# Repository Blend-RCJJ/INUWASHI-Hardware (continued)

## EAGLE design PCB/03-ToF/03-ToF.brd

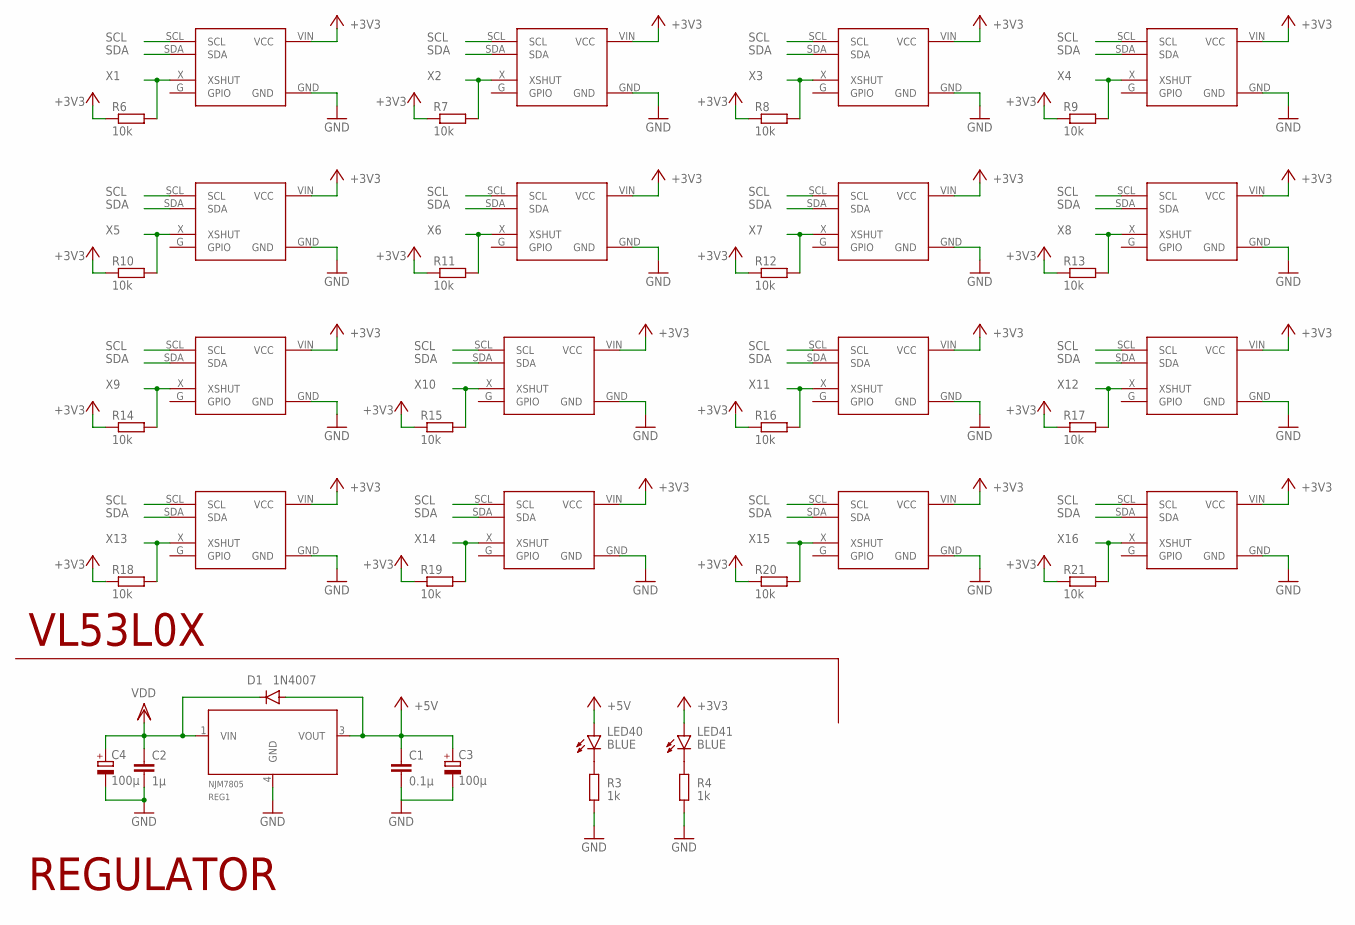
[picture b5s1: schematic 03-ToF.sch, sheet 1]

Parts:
C1: 0.1μ; C0402
C2: 1μ; C0402
C3, C4: 100μ; 153CLV-0505
D1: 1N4007; SMA-DO214AC
LED40, LED41: BLUE; SML0603
R3, R4: 1k; R0402
R6, R7, R8, R9, R10, R11, R12, R13, R14, R15, R16, R17, R18, R19, R20, R21: 10k; R0402
REG1: NJM7805; MYPARTS_D-PAK_TO252AA
VL1, VL2, VL3, VL4, VL5, VL6, VL7, VL8, VL9, VL10, VL11, VL12, VL13, VL14, VL15, VL16: VL53L0X; 1X04

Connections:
+3V3: LED41.A, R6.1, R7.1, R8.1, R9.1, R10.1, R11.1, R12.1, R13.1, R14.1, R15.1, R16.1, R17.1, R18.1, R19.1, R20.1, R21.1, VL1.VIN (VCC), VL2.VIN (VCC), VL3.VIN (VCC), VL4.VIN (VCC), VL5.VIN (VCC), VL6.VIN (VCC), VL7.VIN (VCC), VL8.VIN (VCC), VL9.VIN (VCC), VL10.VIN (VCC), VL11.VIN (VCC), VL12.VIN (VCC), VL13.VIN (VCC), VL14.VIN (VCC), VL15.VIN (VCC), VL16.VIN (VCC); also elsewhere on the board
+5V: C1.1, C3.+, D1.A, LED40.A, REG1.3 (VOUT); also elsewhere on the board
GND: C1.2, C2.2, C3.-, C4.-, R3.2, R4.2, REG1.4 (GND), VL1.GND, VL2.GND, VL3.GND, VL4.GND, VL5.GND, VL6.GND, VL7.GND, VL8.GND, VL9.GND, VL10.GND, VL11.GND, VL12.GND, VL13.GND, VL14.GND, VL15.GND, VL16.GND; also elsewhere on the board
unnamed: LED40.C, R3.1
unnamed: LED41.C, R4.1
SCL: VL1.SCL, VL2.SCL, VL3.SCL, VL4.SCL, VL5.SCL, VL6.SCL, VL7.SCL, VL8.SCL, VL9.SCL, VL10.SCL, VL11.SCL, VL12.SCL, VL13.SCL, VL14.SCL, VL15.SCL, VL16.SCL; also elsewhere on the board
SDA: VL1.SDA, VL2.SDA, VL3.SDA, VL4.SDA, VL5.SDA, VL6.SDA, VL7.SDA, VL8.SDA, VL9.SDA, VL10.SDA, VL11.SDA, VL12.SDA, VL13.SDA, VL14.SDA, VL15.SDA, VL16.SDA; also elsewhere on the board
VDD: C2.1, C4.+, D1.K (C), REG1.1 (VIN); also elsewhere on the board
X1: R6.2, VL1.X (XSHUT); also elsewhere on the board
X2: R7.2, VL2.X (XSHUT); also elsewhere on the board
X3: R8.2, VL3.X (XSHUT); also elsewhere on the board
X4: R9.2, VL4.X (XSHUT); also elsewhere on the board
X5: R10.2, VL5.X (XSHUT); also elsewhere on the board
X6: R11.2, VL6.X (XSHUT); also elsewhere on the board
X7: R12.2, VL7.X (XSHUT); also elsewhere on the board
X8: R13.2, VL8.X (XSHUT); also elsewhere on the board
X9: R14.2, VL9.X (XSHUT); also elsewhere on the board
X10: R15.2, VL10.X (XSHUT); also elsewhere on the board
X11: R16.2, VL11.X (XSHUT); also elsewhere on the board
X12: R17.2, VL12.X (XSHUT); also elsewhere on the board
X13: R18.2, VL13.X (XSHUT); also elsewhere on the board
X14: R19.2, VL14.X (XSHUT); also elsewhere on the board
X15: R20.2, VL15.X (XSHUT); also elsewhere on the board
X16: R21.2, VL16.X (XSHUT); also elsewhere on the board

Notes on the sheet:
VL53L0X
REGULATOR

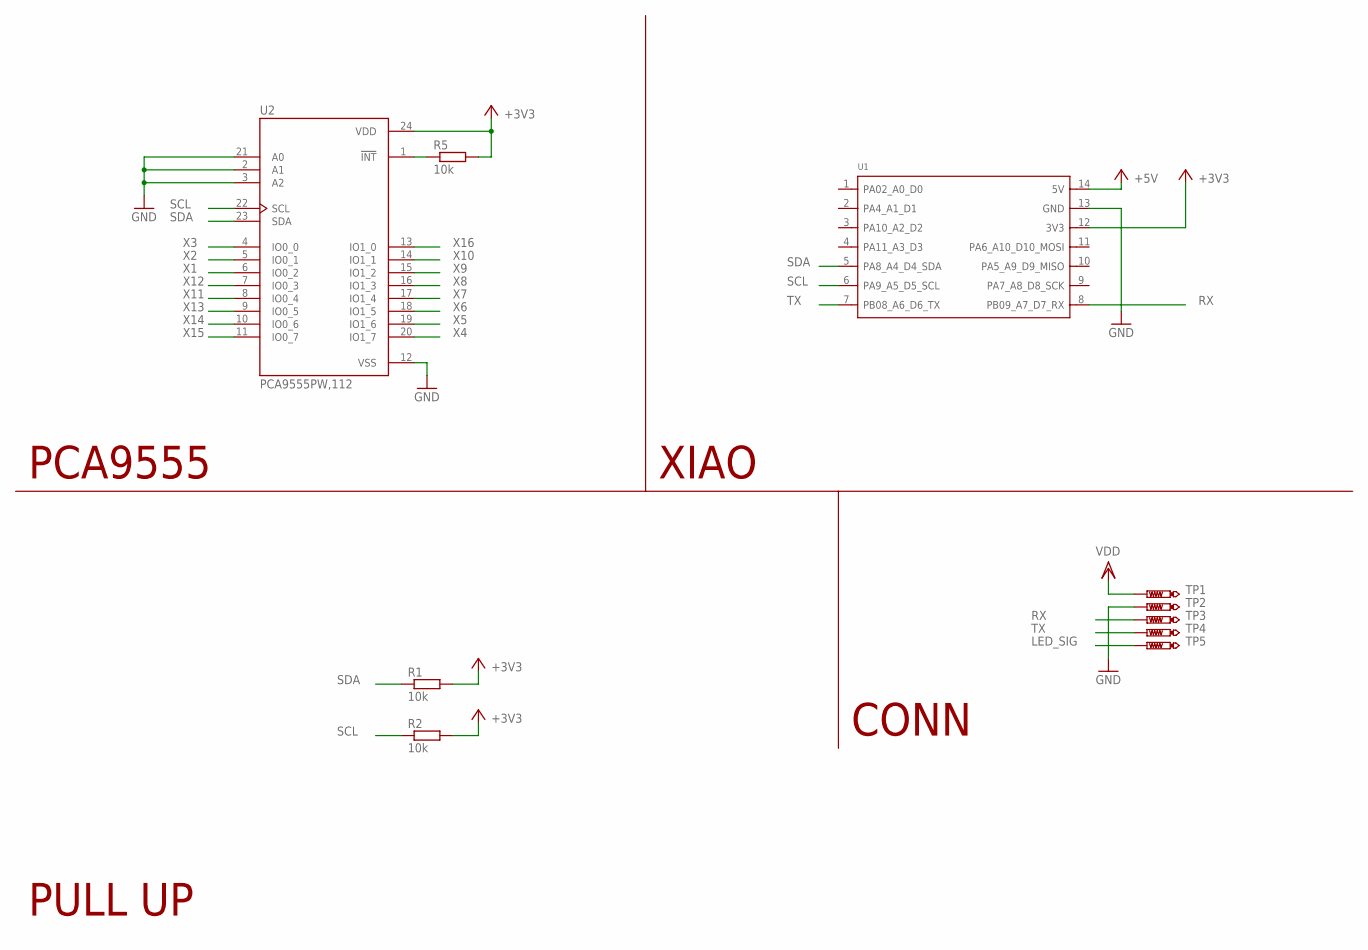
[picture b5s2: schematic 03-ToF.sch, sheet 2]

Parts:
R1, R2, R5: 10k; R0402
TP1, TP3, TP4, TP5: PTR1TP10R; TP10R
TP2: PTR1TP10SQ; TP10SQ
U1: MOUDLE-SEEEDUINO-XIAO; MOUDLE14P-2.54-21X17.8MM
U2: PCA9555PW,112; SOP65P640X110-24N

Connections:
+3V3: R1.2, R2.2, R5.2, U1.12 (3V3), U2.24 (VDD); also elsewhere on the board
+5V: U1.14 (5V); also elsewhere on the board
GND: TP2.TP, U1.13 (GND), U2.2 (A1), U2.3 (A2), U2.12 (VSS), U2.21 (A0); also elsewhere on the board
LED_SIG: TP5.TP; also elsewhere on the board
unnamed: R5.1, U2.1 (!INT)
RX: TP3.TP, U1.8 (PB09_A7_D7_RX)
SCL: R2.1, U1.6 (PA9_A5_D5_SCL), U2.22 (SCL); also elsewhere on the board
SDA: R1.1, U1.5 (PA8_A4_D4_SDA), U2.23 (SDA); also elsewhere on the board
TX: TP4.TP, U1.7 (PB08_A6_D6_TX)
VDD: TP1.TP; also elsewhere on the board
X1: U2.6 (IO0_2); also elsewhere on the board
X2: U2.5 (IO0_1); also elsewhere on the board
X3: U2.4 (IO0_0); also elsewhere on the board
X4: U2.20 (IO1_7); also elsewhere on the board
X5: U2.19 (IO1_6); also elsewhere on the board
X6: U2.18 (IO1_5); also elsewhere on the board
X7: U2.17 (IO1_4); also elsewhere on the board
X8: U2.16 (IO1_3); also elsewhere on the board
X9: U2.15 (IO1_2); also elsewhere on the board
X10: U2.14 (IO1_1); also elsewhere on the board
X11: U2.8 (IO0_4); also elsewhere on the board
X12: U2.7 (IO0_3); also elsewhere on the board
X13: U2.9 (IO0_5); also elsewhere on the board
X14: U2.10 (IO0_6); also elsewhere on the board
X15: U2.11 (IO0_7); also elsewhere on the board
X16: U2.13 (IO1_0); also elsewhere on the board

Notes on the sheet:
PCA9555
PULL UP
CONN
XIAO

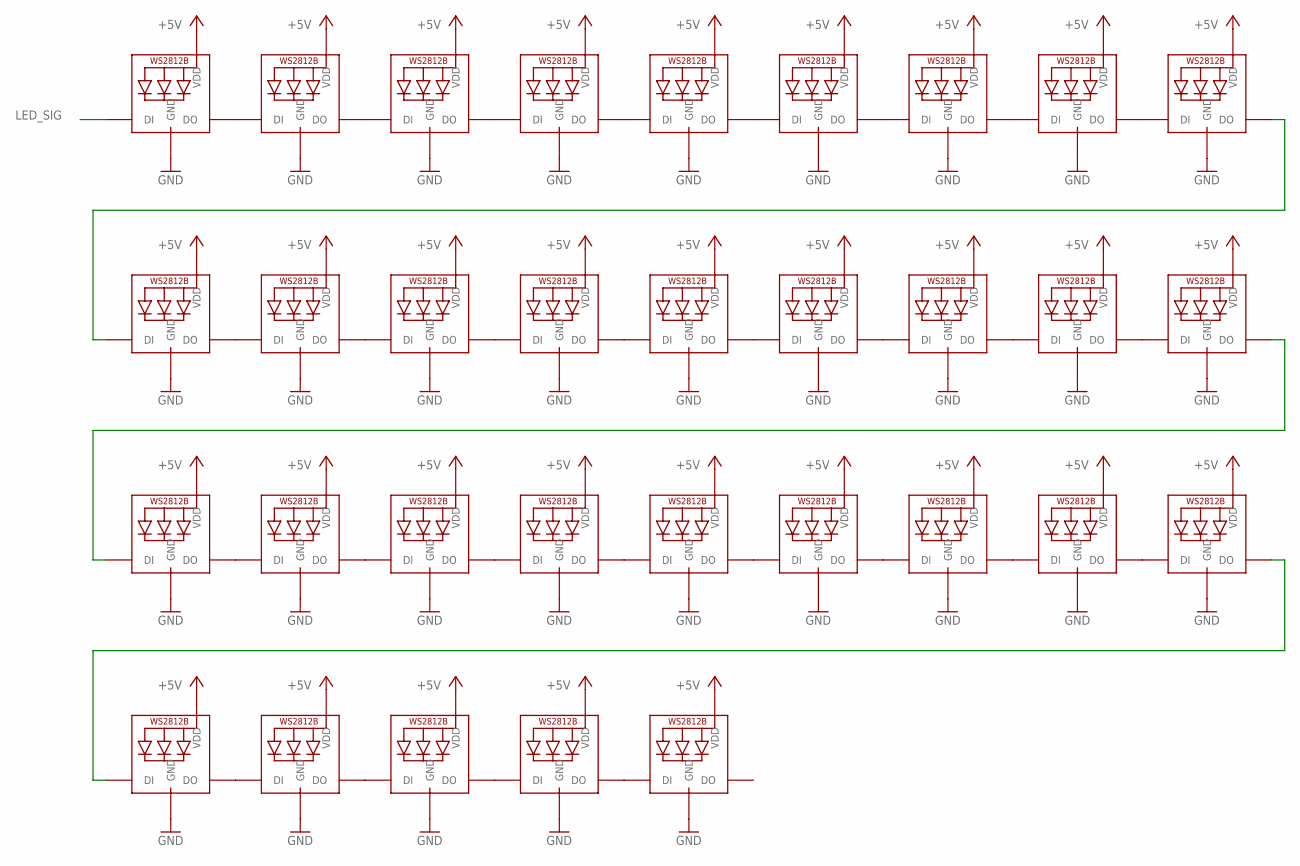
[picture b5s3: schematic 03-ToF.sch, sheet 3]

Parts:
LED1, LED2, LED3, LED4, LED5, LED6, LED7, LED8, LED9, LED10, LED11, LED12, LED13, LED14, LED15, LED16, LED17, LED18, LED19, LED20, LED21, LED22, LED23, LED24, LED25, LED26, LED27, LED28, LED29, LED30, LED31, LED32: WS2812B_5050N; WS2812B-NARROW

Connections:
+5V: LED1.1-VDD (VDD), LED2.1-VDD (VDD), LED3.1-VDD (VDD), LED4.1-VDD (VDD), LED5.1-VDD (VDD), LED6.1-VDD (VDD), LED7.1-VDD (VDD), LED8.1-VDD (VDD), LED9.1-VDD (VDD), LED10.1-VDD (VDD), LED11.1-VDD (VDD), LED12.1-VDD (VDD), LED13.1-VDD (VDD), LED14.1-VDD (VDD), LED15.1-VDD (VDD), LED16.1-VDD (VDD), LED17.1-VDD (VDD), LED18.1-VDD (VDD), LED19.1-VDD (VDD), LED20.1-VDD (VDD), LED21.1-VDD (VDD), LED22.1-VDD (VDD), LED23.1-VDD (VDD), LED24.1-VDD (VDD), LED25.1-VDD (VDD), LED26.1-VDD (VDD), LED27.1-VDD (VDD), LED28.1-VDD (VDD), LED29.1-VDD (VDD), LED30.1-VDD (VDD), LED31.1-VDD (VDD), LED32.1-VDD (VDD); also elsewhere on the board
GND: LED1.3-GND (GND), LED2.3-GND (GND), LED3.3-GND (GND), LED4.3-GND (GND), LED5.3-GND (GND), LED6.3-GND (GND), LED7.3-GND (GND), LED8.3-GND (GND), LED9.3-GND (GND), LED10.3-GND (GND), LED11.3-GND (GND), LED12.3-GND (GND), LED13.3-GND (GND), LED14.3-GND (GND), LED15.3-GND (GND), LED16.3-GND (GND), LED17.3-GND (GND), LED18.3-GND (GND), LED19.3-GND (GND), LED20.3-GND (GND), LED21.3-GND (GND), LED22.3-GND (GND), LED23.3-GND (GND), LED24.3-GND (GND), LED25.3-GND (GND), LED26.3-GND (GND), LED27.3-GND (GND), LED28.3-GND (GND), LED29.3-GND (GND), LED30.3-GND (GND), LED31.3-GND (GND), LED32.3-GND (GND); also elsewhere on the board
LED_SIG: LED1.4-DIN (DI); also elsewhere on the board
unnamed: LED1.2-DOUT (DO), LED2.4-DIN (DI)
unnamed: LED2.2-DOUT (DO), LED3.4-DIN (DI)
unnamed: LED3.2-DOUT (DO), LED4.4-DIN (DI)
unnamed: LED4.2-DOUT (DO), LED5.4-DIN (DI)
unnamed: LED5.2-DOUT (DO), LED6.4-DIN (DI)
unnamed: LED6.2-DOUT (DO), LED7.4-DIN (DI)
unnamed: LED7.2-DOUT (DO), LED8.4-DIN (DI)
unnamed: LED8.2-DOUT (DO), LED9.4-DIN (DI)
unnamed: LED10.2-DOUT (DO), LED11.4-DIN (DI)
unnamed: LED11.2-DOUT (DO), LED12.4-DIN (DI)
unnamed: LED12.2-DOUT (DO), LED13.4-DIN (DI)
unnamed: LED13.2-DOUT (DO), LED14.4-DIN (DI)
unnamed: LED14.2-DOUT (DO), LED15.4-DIN (DI)
unnamed: LED15.2-DOUT (DO), LED16.4-DIN (DI)
unnamed: LED16.2-DOUT (DO), LED17.4-DIN (DI)
unnamed: LED17.2-DOUT (DO), LED18.4-DIN (DI)
unnamed: LED19.2-DOUT (DO), LED20.4-DIN (DI)
unnamed: LED20.2-DOUT (DO), LED21.4-DIN (DI)
unnamed: LED21.2-DOUT (DO), LED22.4-DIN (DI)
unnamed: LED22.2-DOUT (DO), LED23.4-DIN (DI)
unnamed: LED23.2-DOUT (DO), LED24.4-DIN (DI)
unnamed: LED24.2-DOUT (DO), LED25.4-DIN (DI)
unnamed: LED25.2-DOUT (DO), LED26.4-DIN (DI)
unnamed: LED26.2-DOUT (DO), LED27.4-DIN (DI)
unnamed: LED9.2-DOUT (DO), LED10.4-DIN (DI)
unnamed: LED28.2-DOUT (DO), LED29.4-DIN (DI)
unnamed: LED29.2-DOUT (DO), LED30.4-DIN (DI)
unnamed: LED30.2-DOUT (DO), LED31.4-DIN (DI)
unnamed: LED31.2-DOUT (DO), LED32.4-DIN (DI)
unnamed: LED18.2-DOUT (DO), LED19.4-DIN (DI)
unnamed: LED27.2-DOUT (DO), LED28.4-DIN (DI)

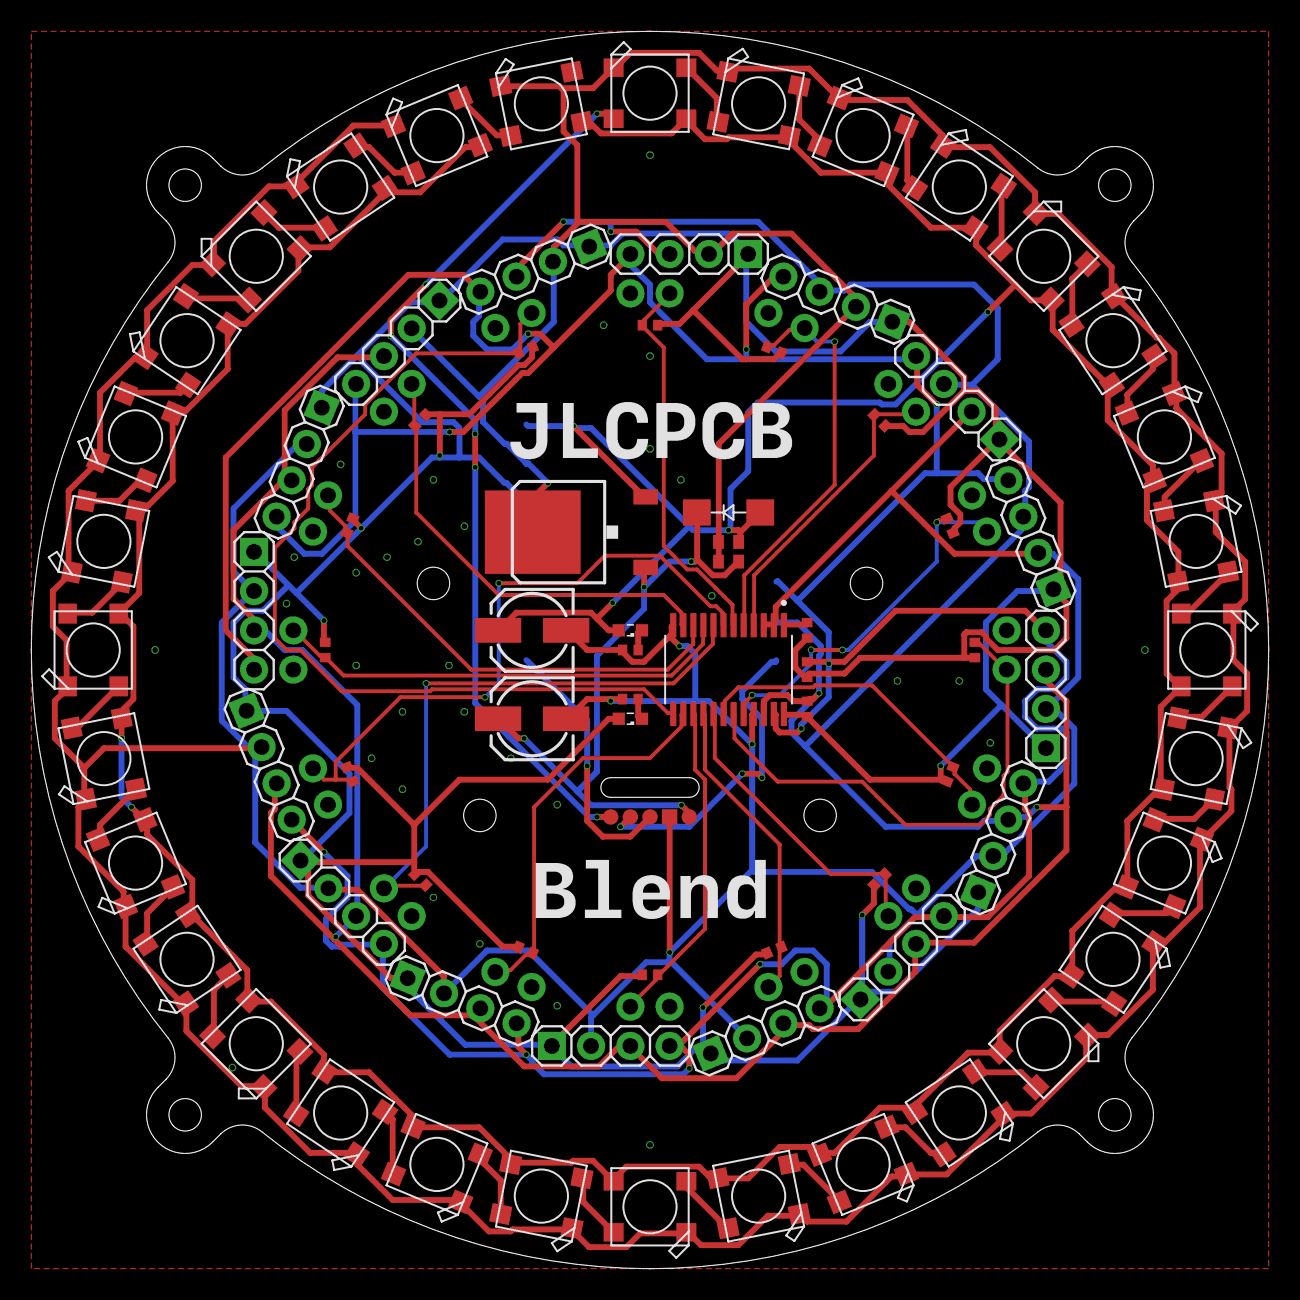
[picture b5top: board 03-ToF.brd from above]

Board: 2 copper layers, 80.0 x 80.0 mm, 84 parts (1 on the bottom side), 59 nets.

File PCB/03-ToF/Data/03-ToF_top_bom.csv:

Comment,Designator,Footprint,LCSC Part #
0.1μ,C1,C0402,C285034
1N4007,D1,SMA-DO214AC,C727081
180,R3 R4,R0402,C38941
1μ,C2,C0402,C52923
10k,R1 R2 R5 R6 R7 R8 R9 R10 R11 R12 R13 R14 R15 R16 R17 R18 R19 R20 R21,R0402,C269674
100μ,C3 C4,153CLV-0505,C269674
BLUE,LED40 LED41,SML0603,C118339
NJM7805,REG1,MYPARTS_D-PAK_TO252AA,
PCA9555PW 112,U2,SOP65P640X110-24N,C128392
WS2812B_5050N,LED1 LED2 LED3 LED4 LED5 LED6 LED7 LED8 LED9 LED10 LED11 LED12 LED13 LED14 LED15 LED16 LED17 LED18 LED19 LED20 LED21 LED22 LED23 LED24 LED25 LED26 LED27 LED28 LED29 LED30 LED31 LED32,WS2812B-NARROW,C2874885

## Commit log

2023-05-21 基板類全部
2023-05-21 ToFレイアウト完了
2023-05-21 配置微調整
2023-05-21 03-tof
2023-05-22 電源基板完成
2023-05-23 02-ui
2023-05-25 main配置完了
2023-05-25 メイン配線完了
2023-05-30 配置完了
2023-05-30 人生楽ありゃ苦もあるさ
2023-05-30 にゅーぷるあっぷ
2023-05-30 配線完了！！
2023-05-30 Revert "ねこ"
    This reverts commit a85c6a9ac54e5e413855fdb3eef226a7b30d2926.
2023-05-30 Revert "配線完了！！"
    This reverts commit 358a7b28429e96d6d805ade8accdc2bc4b7907af.
2023-05-30 今度こそ配置完了？
2023-05-30 mantaray
2023-05-31 メイン配置おわ
2023-05-31 ちびちび
2023-05-31 wet cat
2023-06-02 書き出し
